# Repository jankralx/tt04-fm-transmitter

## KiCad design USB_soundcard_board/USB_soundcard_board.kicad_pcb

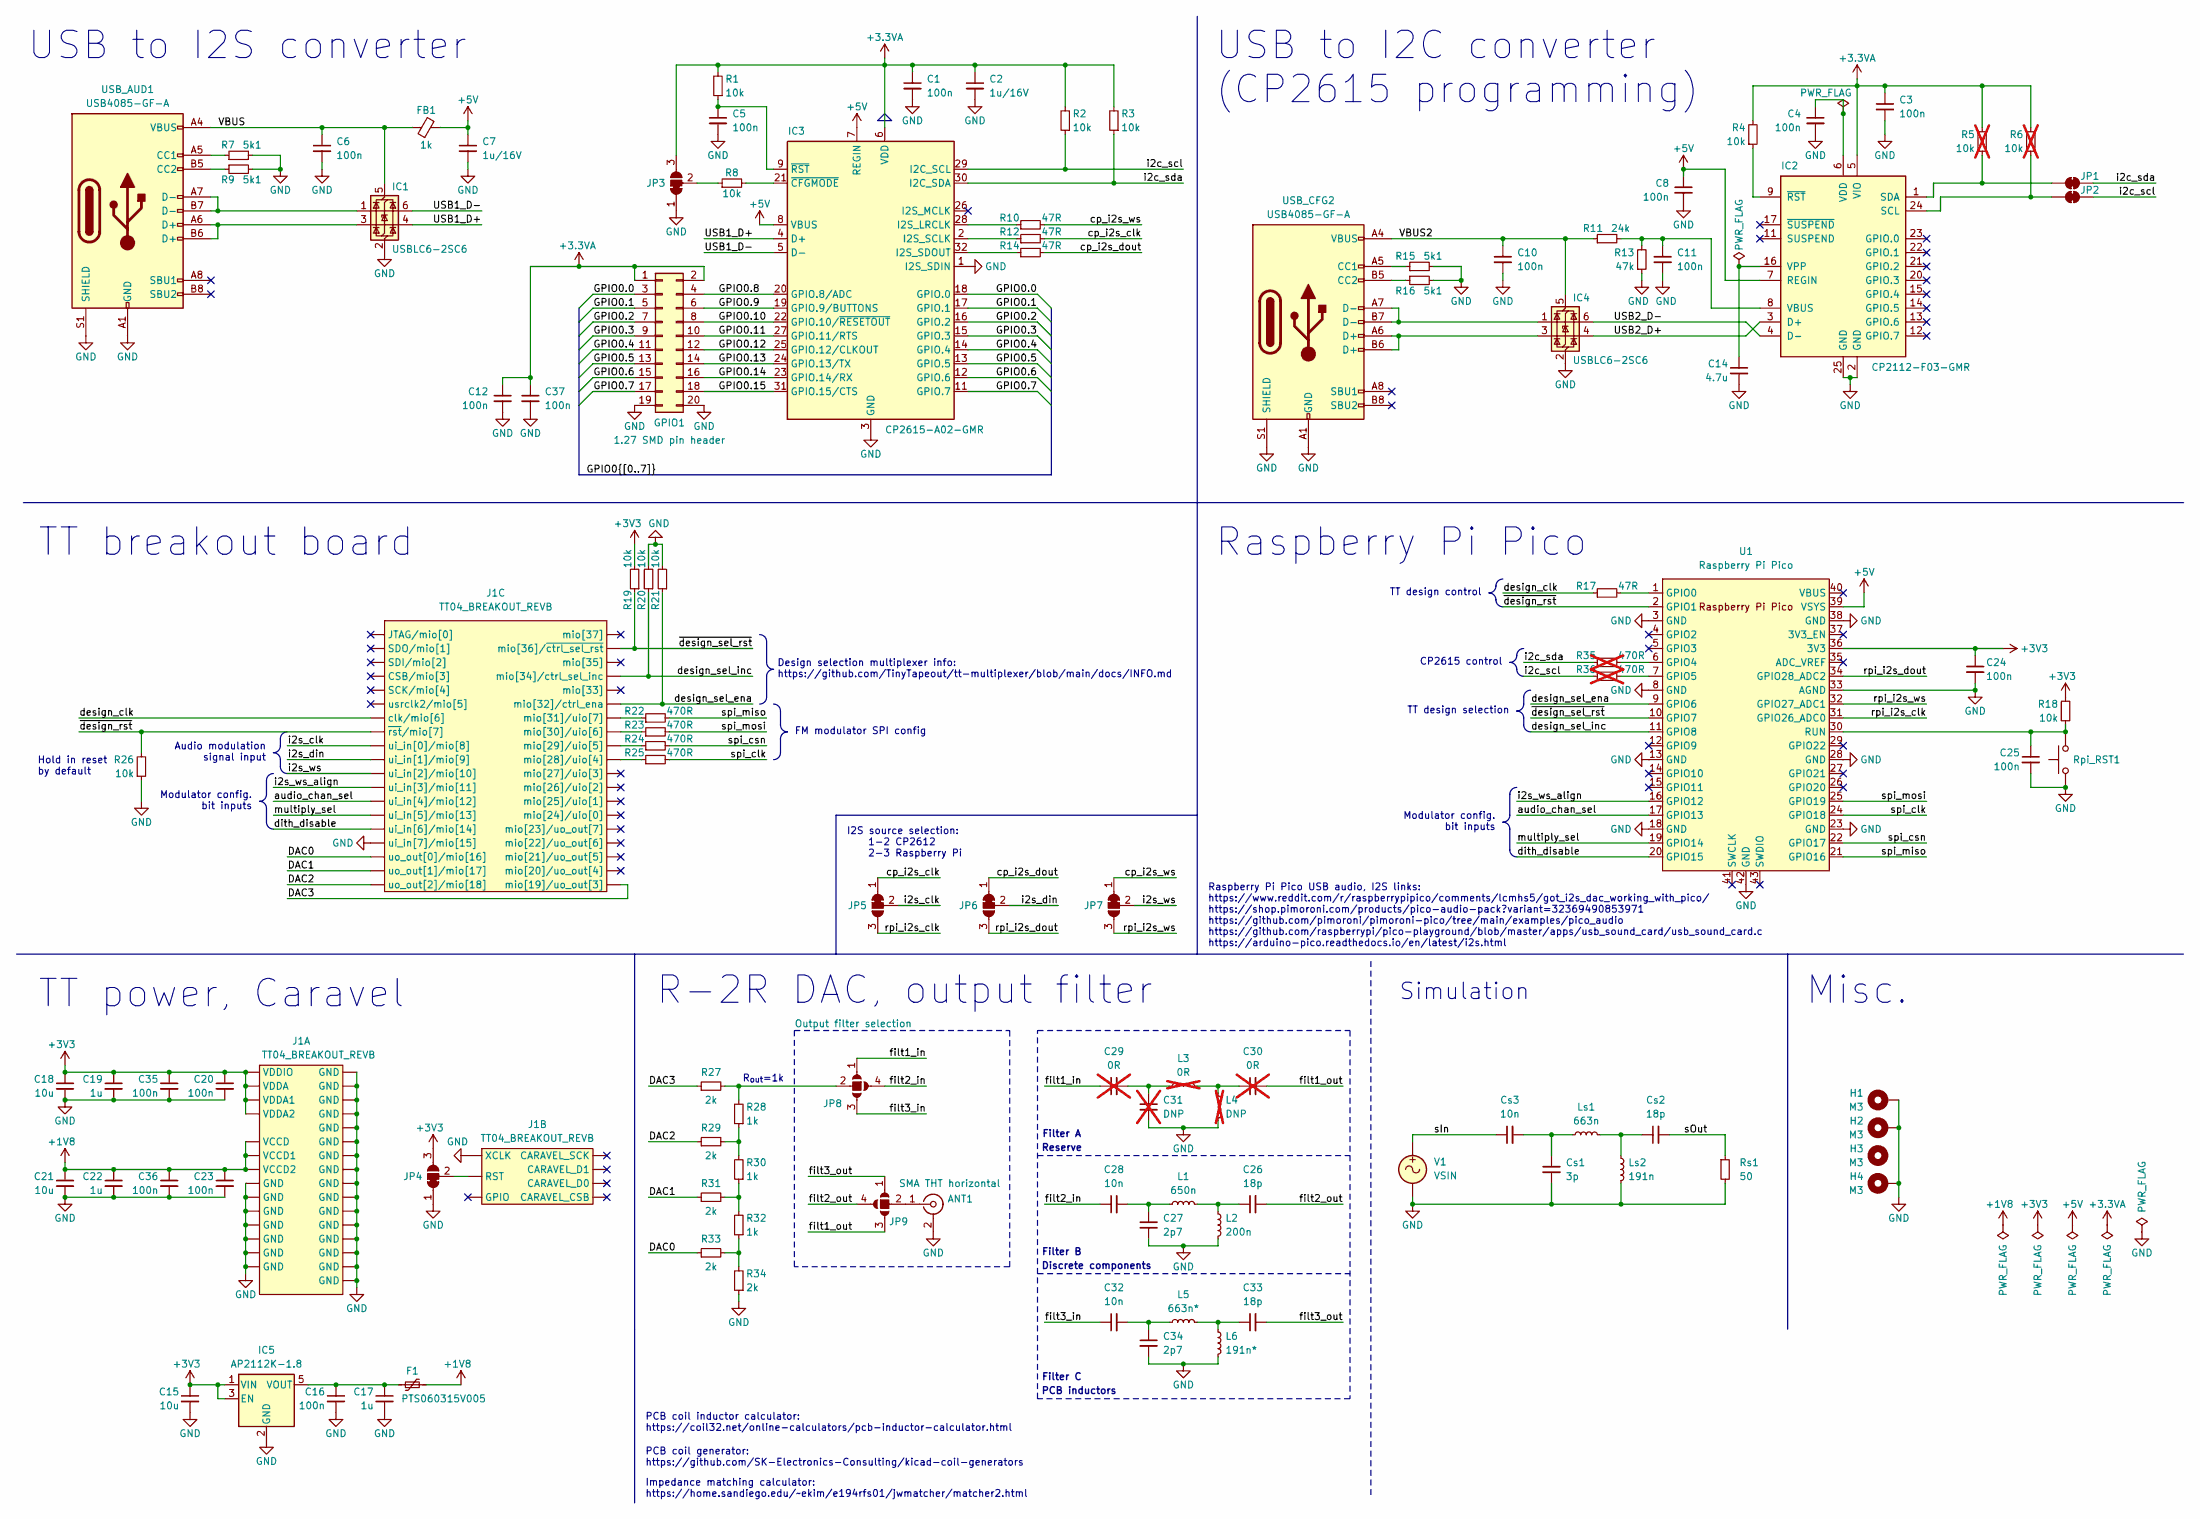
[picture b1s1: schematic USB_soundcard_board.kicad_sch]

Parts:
ANT1: SMA THT horizontal; SMA_Amphenol_132203-12_Horizontal
C1, C3, C4, C5, C6, C8, C10, C11, C12, C16, C20, C23, C24, C25, C35, C36, C37: 100n; C_0603_1608Metric_Pad1.08x0.95mm_HandSolder
C2, C7: 1u/16V; C_0603_1608Metric_Pad1.08x0.95mm_HandSolder
C14: 4.7u; C_0805_2012Metric_Pad1.18x1.45mm_HandSolder
C15, C18, C21: 10u; C_0805_2012Metric_Pad1.18x1.45mm_HandSolder
C17, C19, C22: 1u; C_0603_1608Metric_Pad1.08x0.95mm_HandSolder
C26, C33: 18p; C_0603_1608Metric_Pad1.08x0.95mm_HandSolder
C27, C34: 2p7; C_0603_1608Metric_Pad1.08x0.95mm_HandSolder
C28, C32: 10n; C_0603_1608Metric_Pad1.08x0.95mm_HandSolder
C29, C30: 0R; C_0603_1608Metric_Pad1.08x0.95mm_HandSolder; not fitted
C31: DNP; C_0603_1608Metric_Pad1.08x0.95mm_HandSolder; not fitted
Cs1: 3p
Cs2: 18p
Cs3: 10n
F1: PTS060315V005; Fuse_0603_1608Metric_Pad1.05x0.95mm_HandSolder
FB1: 1k; L_0805_2012Metric_Pad1.15x1.40mm_HandSolder
GPIO1: 1.27 SMD pin header; PinHeader_2x10_P1.27mm_Vertical_SMD
H1, H2, H4: M3; MountingHole_3.2mm_M3_Pad_Via
H3: M3; MountingHole_3.2mm_M3
IC1, IC4: USBLC6-2SC6; SOT-23-6_Handsoldering
IC2: CP2112-F03-GMR; QFN-24-1EP_4x4mm_P0.5mm_EP2.6x2.6mm_ThermalVias
IC3: CP2615-A02-GMR; QFN-32-1EP_5x5mm_P0.5mm_EP3.3x3.3mm_ThermalVias
IC5: AP2112K-1.8; SOT-23-5
J1: TT04_BREAKOUT_REVB; TT04_BREAKOUT_SMB
JP1, JP2: SolderJumper_2_Bridged; SolderJumper-2_P1.3mm_Bridged_RoundedPad1.0x1.5mm
JP3, JP4, JP5, JP6, JP7: SolderJumper_3_Bridged12; SolderJumper-3_P1.3mm_Bridged12_RoundedPad1.0x1.5mm_NumberL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
JP8, JP9: Output filter selection; SolderJumper-4_P1.3mm_Open_RoundedPad1.0x1.5mm_NumberLabels
L1: 650n; L_0603_1608Metric_Pad1.05x0.95mm_HandSolder
L2: 200n; L_0603_1608Metric_Pad1.05x0.95mm_HandSolder
L3: 0R; L_0603_1608Metric_Pad1.05x0.95mm_HandSolder; not fitted
L4: DNP; L_0603_1608Metric_Pad1.05x0.95mm_HandSolder; not fitted
L5: 663n*; Inductor_663nH
L6: 191n*; Inductor_191nH
Ls1: 663n
Ls2: 191n
R1, R2, R3, R4, R8, R18, R19, R20, R21, R26: 10k; R_0603_1608Metric_Pad0.98x0.95mm_HandSolder
R5, R6: 10k; R_0603_1608Metric_Pad0.98x0.95mm_HandSolder; not fitted
R7, R9, R15, R16: 5k1; R_0603_1608Metric_Pad0.98x0.95mm_HandSolder
R10, R12, R14, R17: 47R; R_0603_1608Metric_Pad0.98x0.95mm_HandSolder
R11: 24k; R_0603_1608Metric_Pad0.98x0.95mm_HandSolder
R13: 47k; R_0603_1608Metric_Pad0.98x0.95mm_HandSolder
R22, R23, R24, R25: 470R; R_0603_1608Metric_Pad0.98x0.95mm_HandSolder
R27, R29, R31, R33, R34: 2k; R_0603_1608Metric_Pad0.98x0.95mm_HandSolder
R28, R30, R32: 1k; R_0603_1608Metric_Pad0.98x0.95mm_HandSolder
R35, R36: 470R; R_0603_1608Metric_Pad0.98x0.95mm_HandSolder; not fitted
Rpi_RST1: Raspberry Pi reset; SW_Tactile_SPST_NO_Straight_CK_PTS636Sx25SMTRLFS
Rs1: 50
U1: Raspberry Pi Pico; RPi_Pico_SMD_TH
USB_AUD1: USB4085-GF-A; USB_C_Receptacle_GCT_USB4085
USB_CFG2: USB4085-GF-A; USB_C_Receptacle_GCT_USB4085
V1: VSIN

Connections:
+1V8: C21.1, C22.1, C23.1, C36.1, F1.2, J1.A7 (VCCD), J1.B14 (VCCD2), J1.B16 (VCCD2), J1.B33 (VCCD1), J1.B35 (VCCD1)
+3.3VA: C1.1, C2.1, C3.1, C12.1, C37.1, GPIO1.1, GPIO1.2, IC2.5 (VIO), IC3.6 (VDD), JP3.3 (B), R1.2, R2.2, R3.2, R4.2, R5.2, R6.2
+3V3: C15.1, C18.1, C19.1, C20.1, C24.1, C35.1, IC5.1 (VIN), IC5.3 (EN), J1.A19 (VDDA), J1.B1 (VDDA2), J1.B3 (VDDA2), J1.B15 (VDDIO), J1.B17 (VDDIO), J1.B37 (VDDA1), J1.B39 (VDDA1), JP4.3 (B), R18.2, R19.2, U1.36 (3V3)
+5V: C7.1, C8.1, FB1.2, IC2.7 (REGIN), IC3.7 (REGIN), IC3.8 (VBUS), U1.39 (VSYS)
/DAC0: J1.B32 (uo_out[0]/mio[16]), R33.1
/DAC1: J1.B29 (uo_out[1]/mio[17]), R31.1
/DAC2: J1.B30 (uo_out[2]/mio[18]), R29.1
/DAC3: J1.B27 (mio[19]/uo_out[3]), R27.1
/GPIO0.0: GPIO1.3, IC3.18 (GPIO.0)
/GPIO0.1: GPIO1.5, IC3.17 (GPIO.1)
/GPIO0.2: GPIO1.7, IC3.16 (GPIO.2)
/GPIO0.3: GPIO1.9, IC3.15 (GPIO.3)
/GPIO0.4: GPIO1.11, IC3.14 (GPIO.4)
/GPIO0.5: GPIO1.13, IC3.13 (GPIO.5)
/GPIO0.6: GPIO1.15, IC3.12 (GPIO.6)
/GPIO0.7: GPIO1.17, IC3.11 (GPIO.7)
/GPIO0.8: GPIO1.4, IC3.20 (GPIO.8/ADC)
/GPIO0.9: GPIO1.6, IC3.19 (GPIO.9/BUTTONS)
/GPIO0.10: GPIO1.8, IC3.22 (GPIO.10/~RESETOUT)
/GPIO0.11: GPIO1.10, IC3.27 (GPIO.11/RTS)
/GPIO0.12: GPIO1.12, IC3.25 (GPIO.12/CLKOUT)
/GPIO0.13: GPIO1.14, IC3.24 (GPIO.13/TX)
/GPIO0.14: GPIO1.16, IC3.23 (GPIO.14/RX)
/GPIO0.15: GPIO1.18, IC3.31 (GPIO.15/CTS)
/USB1_D+: IC1.4 (I/O2), IC3.4 (D+)
/USB1_D-: IC1.6 (I/O1), IC3.5 (D-)
/USB2_D+: IC2.3 (D+), IC4.4 (I/O2)
/USB2_D-: IC2.4 (D-), IC4.6 (I/O1)
/VBUS: C6.1, FB1.1, IC1.5 (VBUS), USB_AUD1.A4 (VBUS), USB_AUD1.A9 (VBUS), USB_AUD1.B4 (VBUS), USB_AUD1.B9 (VBUS)
/VBUS2: C10.1, IC4.5 (VBUS), R11.1, USB_CFG2.A4 (VBUS), USB_CFG2.A9 (VBUS), USB_CFG2.B4 (VBUS), USB_CFG2.B9 (VBUS)
/audio_chan_sel: J1.A36 (ui_in[4]/mio[12]), U1.17 (GPIO13)
/cp_i2s_clk: JP5.1 (A), R12.2
/cp_i2s_dout: JP6.1 (A), R14.2
/cp_i2s_ws: JP7.1 (A), R10.2
/design_clk: J1.A28 (clk/mio[6]), R17.1
/design_sel_ena: J1.A1 (mio[32]/ctrl_ena), R21.1, U1.9 (GPIO6)
/design_sel_inc: J1.A3 (mio[34]/ctrl_sel_inc), R20.1, U1.11 (GPIO8)
/dith_disable: J1.A38 (ui_in[6]/mio[14]), U1.20 (GPIO15)
/filt1_in: C29.1, JP8.1 (A)
/filt1_out: C30.2, JP9.3 (B)
/filt2_in: C28.1, JP8.4 (D)
/filt2_out: C26.2, JP9.4 (D)
/filt3_in: C32.1, JP8.3 (B)
/filt3_out: C33.2, JP9.1 (A)
/i2c_scl: IC3.29 (I2C_SCL), JP2.2 (B), R2.1, R36.1
/i2c_sda: IC3.30 (I2C_SDA), JP1.2 (B), R3.1, R35.1
/i2s_clk: J1.A32 (ui_in[0]/mio[8]), JP5.2 (C)
/i2s_din: J1.A33 (ui_in[1]/mio[9]), JP6.2 (C)
/i2s_ws: J1.A34 (ui_in[2]/mio[10]), JP7.2 (C)
/i2s_ws_align: J1.A35 (ui_in[3]/mio[11]), U1.16 (GPIO12)
/multiply_sel: J1.A37 (ui_in[5]/mio[13]), U1.19 (GPIO14)
/rpi_i2s_clk: JP5.3 (B), U1.31 (GPIO26_ADC0)
/rpi_i2s_dout: JP6.3 (B), U1.34 (GPIO28_ADC2)
/rpi_i2s_ws: JP7.3 (B), U1.32 (GPIO27_ADC1)
/spi_clk: R25.2, U1.24 (GPIO18)
/spi_csn: R24.2, U1.22 (GPIO17)
/spi_miso: R22.2, U1.21 (GPIO16)
/spi_mosi: R23.2, U1.25 (GPIO19)
/~design_rst: J1.A31 (~rst/mio[7]), R26.2, U1.2 (GPIO1)
/~design_sel_rst: J1.A8 (mio[36]/~ctrl_sel_rst), R19.1, U1.10 (GPIO7)
GND: ANT1.2 (Ext), C1.2, C2.2, C3.2, C4.2, C5.2, C6.2, C7.2, C8.2, C10.2, C11.2, C12.2, C14.2, C15.2, C16.2, C17.2, C18.2, C19.2, C20.2, C21.2, C22.2, C23.2, C24.2, C25.2, C27.2, C31.2, C34.2, C35.2, C36.2, C37.2, Cs1.2, GPIO1.19, GPIO1.20, H1.1, H2.1, H4.1, IC1.2 (GND), IC2.2 (GND), IC2.25 (GND), IC3.1 (I2S_SDIN), IC3.3 (GND), IC3.33 (GND), IC4.2 (GND), IC5.2 (GND), J1.A2 (GND), J1.A9 (GND), J1.A10 (GND), J1.A11 (XCLK), J1.A15 (GND), J1.A20 (GND), J1.A25 (GND), J1.A29 (GND), J1.A30 (GND), J1.A39 (ui_in[7]/mio[15]), J1.A40 (GND), J1.B2 (GND), J1.B4 (GND), J1.B12 (GND), J1.B13 (GND), J1.B18 (GND), J1.B19 (GND), J1.B20 (GND), J1.B24 (GND), J1.B25 (GND), J1.B31 (GND), J1.B34 (GND), J1.B36 (GND), J1.B38 (GND), J1.B40 (GND), JP3.1 (A), JP4.1 (A), L2.2, L4.2, L6.2, Ls2.2, R7.2, R9.2, R13.1, R15.2, R16.2, R20.2, R21.2, R26.1, R34.1, Rpi_RST1.1, Rs1.2, U1.3 (GND), U1.8 (GND), U1.13 (GND), U1.18 (GND), U1.23 (GND), U1.28 (GND), U1.33 (AGND), U1.38 (GND), U1.42 (GND), USB_AUD1.A1 (GND), USB_AUD1.A12 (GND), USB_AUD1.B1 (GND), USB_AUD1.B12 (GND), USB_AUD1.S1 (SHIELD), USB_CFG2.A1 (GND), USB_CFG2.A12 (GND), USB_CFG2.B1 (GND), USB_CFG2.B12 (GND), USB_CFG2.S1 (SHIELD), V1.2
unnamed: ANT1.1 (In), JP9.2 (C)
unnamed: C26.1, L1.2, L2.1
unnamed: C27.1, C28.2, L1.1
unnamed: C29.2, C31.1, L3.1
unnamed: C30.1, L3.2, L4.1
unnamed: C32.2, C34.1, L5.1
unnamed: C33.1, L5.2, L6.1
unnamed: Cs1.1, Cs3.2, Ls1.1
unnamed: Cs2.1, Ls1.2, Ls2.1
unnamed: Cs2.2, Rs1.1
unnamed: Cs3.1, V1.1
unnamed: IC1.1 (I/O1), USB_AUD1.A7 (D-), USB_AUD1.B7 (D-)
unnamed: IC1.3 (I/O2), USB_AUD1.A6 (D+), USB_AUD1.B6 (D+)
unnamed: IC2.24 (SCL), JP2.1 (A), R6.1
unnamed: IC2.1 (SDA), JP1.1 (A), R5.1
unnamed: C11.1, IC2.8 (VBUS), R11.2, R13.2
unnamed: C4.1, IC2.6 (VDD)
unnamed: C14.1, IC2.16 (VPP)
unnamed: IC2.9 (~RST), R4.1
unnamed: IC3.28 (I2S_LRCLK), R10.1
unnamed: IC3.2 (I2S_SCLK), R12.1
unnamed: IC3.32 (I2S_SDOUT), R14.1
unnamed: IC3.21 (~CFGMODE), R8.2
unnamed: C5.1, IC3.9 (~RST), R1.1
unnamed: IC4.1 (I/O1), USB_CFG2.A7 (D-), USB_CFG2.B7 (D-)
unnamed: IC4.3 (I/O2), USB_CFG2.A6 (D+), USB_CFG2.B6 (D+)
unnamed: C16.1, C17.1, F1.1, IC5.5 (VOUT)
unnamed: J1.A12 (RST), JP4.2 (C)
unnamed: J1.B7 (mio[28]/uio[4]), R25.1
unnamed: J1.B8 (mio[29]/uio[5]), R24.1
unnamed: J1.B5 (mio[30]/uio[6]), R23.1
unnamed: J1.B6 (mio[31]/uio[7]), R22.1
unnamed: JP3.2 (C), R8.1
unnamed: JP8.2 (C), R27.2, R28.2
unnamed: R28.1, R29.2, R30.2
unnamed: R30.1, R31.2, R32.2
unnamed: R32.1, R33.2, R34.2
unnamed: R17.2, U1.1 (GPIO0)
unnamed: R35.2, U1.6 (GPIO4)
unnamed: R36.2, U1.7 (GPIO5)
unnamed: C25.1, R18.1, Rpi_RST1.2, U1.30 (RUN)
unnamed: R7.1, USB_AUD1.A5 (CC1)
unnamed: R9.1, USB_AUD1.B5 (CC2)
unnamed: R15.1, USB_CFG2.A5 (CC1)
unnamed: R16.1, USB_CFG2.B5 (CC2)

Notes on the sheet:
Modulator config. bit inputs
TT power, Caravel
I2S source selection: 1-2 CP2612 2-3 Raspberry Pi
Design selection multiplexer info: https://github.com/TinyTapeout/tt-multiplexer/blob/main/docs/INFO.md
USB to I2S converter
CP2615 control
Filter A
PCB inductors
PCB coil generator: https://github.com/SK-Electronics-Consulting/kicad-coil-generators
Audio modulation signal input
Raspberry Pi Pico USB audio, I2S links: https://www.reddit.com/r/raspberrypipico/comments/lcmhs5/got_i2s_dac_working_with_pico/ https://shop.pimoroni.com/products/pico-audio-pack?variant=32369490853971 https://github.com/pimoroni/pimoroni-pico/tree/main/examples/pico_audio https://github.com/raspbe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
Misc.
PCB coil inductor calculator: https://coil32.net/online-calculators/pcb-inductor-calculator.html
Impedance matching calculator: https://home.sandiego.edu/~ekim/e194rfs01/jwmatcher/matcher2.html
Discrete components
Hold in reset by default
Filter B
Filter C
R-2R DAC, output filter
USB to I2C converter (CP2615 programming)
R_{out}=1k
TT design control
TT breakout board
FM modulator SPI config
TT design selection
Reserve
Simulation
Raspberry Pi Pico

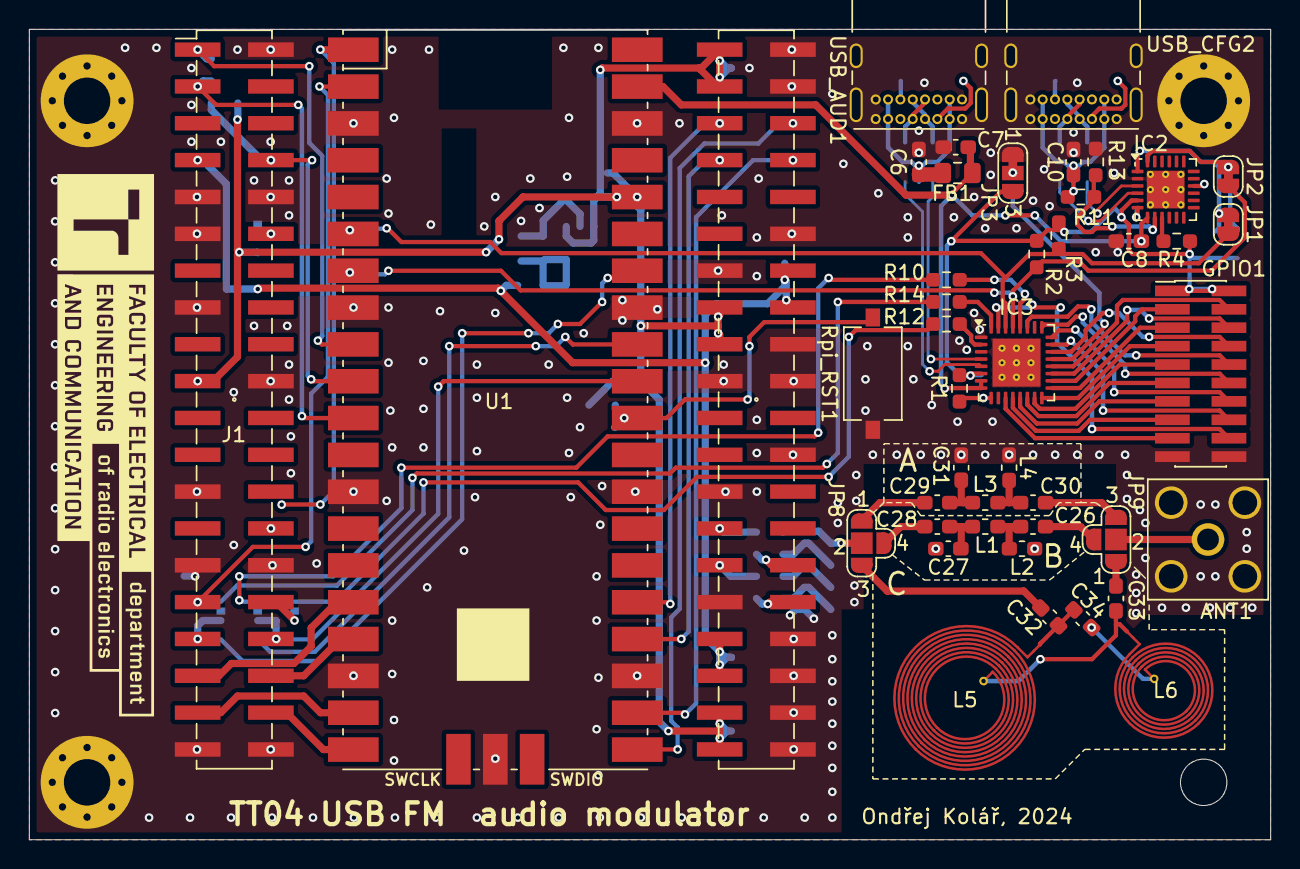
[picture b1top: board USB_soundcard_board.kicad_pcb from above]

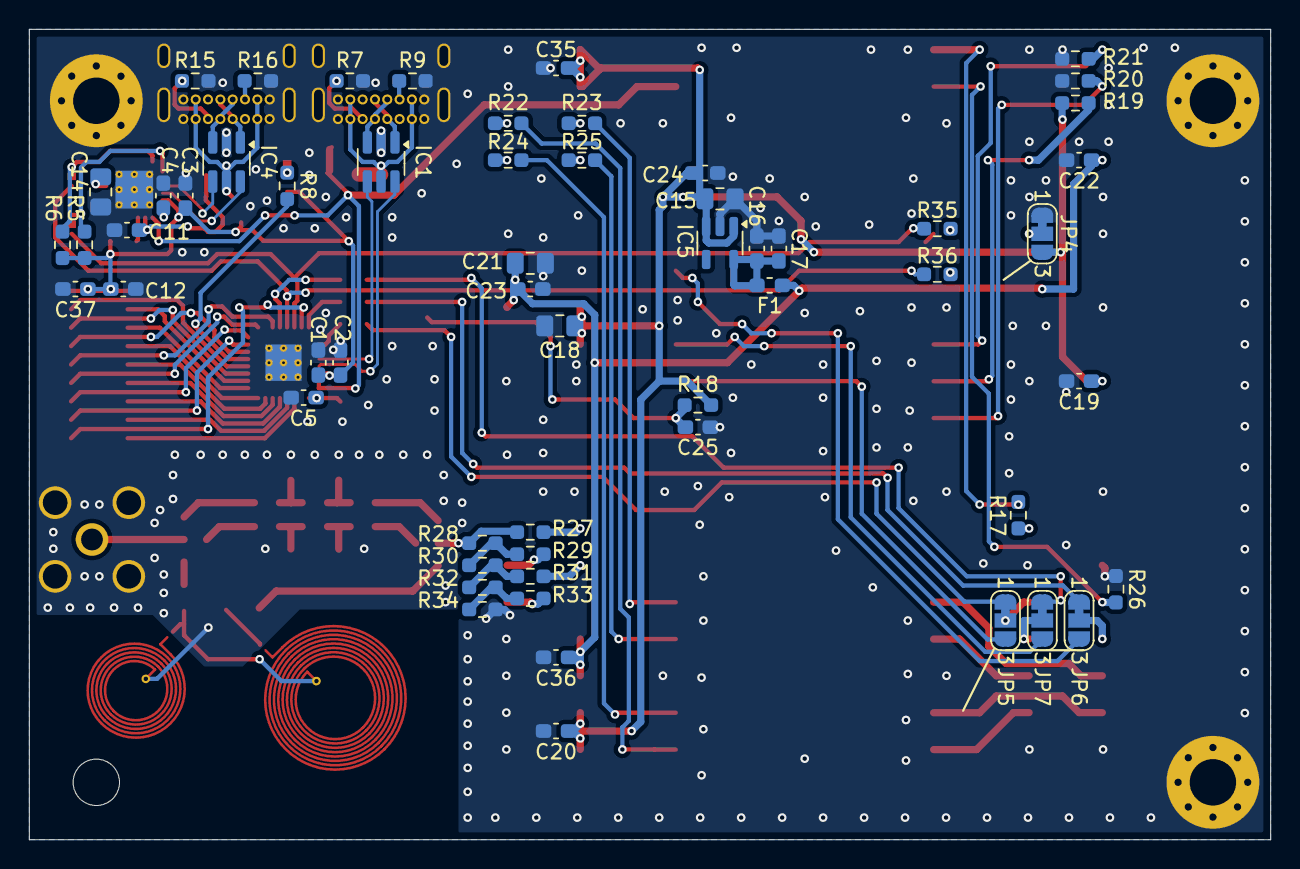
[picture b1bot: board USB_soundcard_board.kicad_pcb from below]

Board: 2 copper layers, 85.6 x 55.9 mm, 104 parts (57 on the bottom side), 102 nets.

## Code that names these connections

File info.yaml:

--- 
# TinyTapeout project information
project:
  wokwi_id:    0        # If using wokwi, set this to your project's ID

# If using an HDL, set wokwi_id as 0 and uncomment and list your source files here. 
# Source files must be in ./src and you must list each source file separately
  source_files:        
    - fm_modulator.v
    - i2s_rx.v
    - tt_um_fm_transmitter.v
    - cdc_slow2fast_bus.v
    - spi_config.v
  top_module:  "tt_um_fm_transmitter"      # Put the name of your top module here, must start with "tt_um_". Make it unique by including your github username

# How many tiles your design occupies? A single tile is about 167x108 uM.
  tiles: "1x1"    # Valid values: 1x1, 1x2, 2x2, 4x2 or 8x2

# Keep a track of the submission yaml
yaml_version: 4

# As everyone will have access to all designs, try to make it easy for someone new to your design to know what
# it does and how to operate it. This info will be automatically collected and used to make a datasheet for the chip.
#
# Here is a great example: https://github.com/davidsiaw/tt02-davidsiaw-stackcalc/blob/38c5647f83aad2aec675d566aa3d67b98f0aac81/info.yaml
documentation: 
  author:       "Jan Kral (<jan.kral@vut.cz>), Ondrej Kolar (<ondrej.kolar@vut.cz>)"               # Your name
  title:        "FM Transmitter"                       # Project title
  language:     "Verilog"                              # other examples include Verilog, Amaranth, VHDL, etc
  description:  "FM transmitter with I2S input"        # Short description of what your project does

# Longer description of how the project works. You can use standard markdown format.
  how_it_works: |
    Our design takes an audio signal and modulates it to a higher carrier frequency, using [*FM modulation*](https://en.wikipedia.org/wiki/Frequency_modulation). The modulator in our design is based on a [*numerically controlled oscillator*](https://en.wikipedia.org/wiki/Numerically_controlled_oscillator) (NCO) with several modifications.
    
    The *frequency control word*, which increments the *phase accumulator*, is being added with the audio signal. This results in the phase increments proportional to the current audio sample level. The variation directly determines the actual shift of the output signal frequency. For the conversion of phase to a harmonic signal (sine wave) NCOs usually use look-up tables or [*CORDIC algorithm*](https://en.wikipedia.org/wiki/CORDIC). However, both of these methods are resource-heavy, therefore the design adopts a very rough, piecewise linearized approximation of the sine function. The main upside of this approach is the lightweight implementation, which utilizes only simple bit-shifting and addition operations.
    
    ![Our harmonic function approximation](doc/figureApproximation.png)
    
    Since the output digital-to-analog converter suggested below is not followed by a [*reconstruction filter*](https://en.wikipedia.org/wiki/Reconstruction_filter), the output signal will not be present only on a single frequency but also on several higher ones, sometimes called *mirrors* (as they appear on frequencies mirrored by the sampling frequency and its multiples). Thanks to this, it is possible to get the signal in the range of FM broadcast band, even with the sampling frequency lower than the carrier frequency.
    

# Instructions on how someone could test your project, include things like what buttons do what and how to set the clock if needed
  how_to_test:  |
    **Disclaimer! Our design is not intended for real *on air* use. Any signals generated by our design are far from ideal and require proper filtering. Improper use will most probably violate your local regulations. Use only at your own risk!**
    
    ![Schematic of a simple DAC](doc/schematicDAC.png)

    For testing the design you need to provide an audio source using the I2S bus interface. You can use for example Raspberry Pi. For the output, you need to build a DAC. A simple [*R–2R resistor ladder network*](https://en.wikipedia.org/wiki/Resistor_ladder#R%E2%80%932R_resistor_ladder_network_(digital_to_analog_conversion)) should be enough for testing. The schematic is provided above.
   

# A description of what the inputs do (e.g. red button, SPI CLK, SPI MOSI, etc).
  inputs:               
    - i2s_clk
    - i2s_din
    - i2s_ws
    - i2s_ws_align_pin
    - audio_chan_sel_pin
    - multiply_sel_pin
    - dith_disable_pin
    - none
# A description of what the outputs do (e.g. status LED, SPI MISO, etc)
  outputs:
    - dac[0] (LSB)
    - dac[1]
    - dac[2]
    - dac[3] (MSB)
    - none
    - none
    - none
    - none
# A description of what the bidirectional I/O pins do (e.g. I2C SDA, I2C SCL, etc)
  bidirectional:
    - none
    - none
    - none
    - none
    - spi_clk (in)
    - spi_csn (in)
    - spi_mosi (in)
    - spi_miso (inout)

# The following fields are optional
  tag:          "fm, modulator, audio, music, i2s"              # comma separated list of tags: test, encryption, experiment, clock, animation, utility, industrial, pwm, fpga, alu, microprocessor, risc, riscv, sensor, signal generator, fft, filter, music, bcd, sound, serial, timer, random number generator, calculator, decoder, counter, puzzle, multiplier, game, oscillator,
  external_hw:  "4-bit R-2R DAC, I2S source, SPI (optional)"    # Describe any external hardware needed
  discord:      "xkolar74_10263"       # Your discord handle, used for communication and automatically assigning tapeout role after a submission
  doc_link:     "https://github.com/jankralx/tt04-fm-transmitter/blob/main/README.md"      # URL to longer form documentation, eg the README.md in your repository
  clock_hz:     50000000               # Clock frequency in Hz (if required)
  picture:      "doc/diagram.png"      # relative path to a picture in your repository (must be 512kb or less)

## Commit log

2023-08-30 initial commit of files tested on FPGA for FM transmitter
2023-09-04 (src) fixing real type and renaming top design to comply with rules of TT
2023-09-04 (yaml) changing to 1x1 and fixing description
2023-09-04 (documentation) Updated info.yaml and added diagram of the design to 'doc' folder
2023-09-04 (documentation) Added design diagram in PNG, fixed frequency in info.yaml
2023-09-07 (src) spi configuration, FM modulator parameters set by signals
2023-09-07 (info yaml) updated info.yaml to reflect newly defined pins, added source files, and extarnal hardware
2023-09-07 (info yaml) removing URL from names
2023-09-07 (info yaml, src) fixing emails in info yaml and uio_oe in top module
2023-09-07 (src) fixing same instance name in top module
2023-09-07 (src) fixing parameters of modulator instance and negedge sensitivity of spi_clk signal
2023-09-07 (src) chaning MOSI to be given at output on posedge of spi_clk
2023-09-07 (src) fixing two drivers for single nets in top module
2023-09-07 (src) commenting out spi_config to isolate the error source
2023-09-07 (src) adding part of spi_config to isolate the error source
2023-09-07 (src) fixing missing bits in dith_fact assignemnt
2023-09-07 Added some documentation
2023-09-07 Added more documentation and schematics.
2023-09-07 Fixed schematic sizes.
2023-09-07 (FGPA-USB-Device) adding as submodule
2023-09-07 (src) removed unused debug code in spi_config.v
2023-09-07 (src) adding USB support, needs to be connected to FM modulator
2023-09-07 (src) fixing duplicate port assignment in top module
2023-09-08 (src) fixing output to gnd connection in top module
2023-09-08 (src) changing df_inc to df_inc_coef and df_inc_fact for smaller footprint
2023-09-08 (src) fixing selection of multiplexer by df_inc_fact
2023-09-08 (src) trying another implementation of the multiplexer because compilation fails
2023-09-08 (src) fixing width of df_inc_fact and df_inc_coef
2023-09-08 (src) adding negedge sensitive register for spi_miso, and ILAs generated only when part of FPGA project
2023-09-08 (src) version tested on FPGA, fixing some mess with signed wires in FM modulator
2023-09-08 (src) removing negedge register to isolate error source
2023-09-08 (src) fixing asynchronous reset of spi_miso output register
2023-09-08 (src) description modified
2023-09-08 (doc) removing USB from doc
2023-09-08 (doc) fixing margins of schematic-DAC.pdf
2023-09-08 removed submodule of USB as this is not needed
2023-09-08 (doc) adding missing DAC schematic
2023-09-18 (doc) Converted images to PNG.
2023-09-18 (doc) Fixed resolution of images.
2024-08-28 (python) setting python file for FM transmitter
2024-09-09 Added KiCad project of USB soundcard baseboard for the TT04 breakout board.
2024-09-18 Added MicroPython code for the Raspberry Pi Pico on the USB board.
2024-09-18 Post-prototype tweaks in USB board schematic
2025-01-20 Added filter input impedance trace to the simulation.
2025-01-20 (USB_soundcard_board) Added results of filter measurements.
2025-02-19 (doc) Added SDR screenshots.
2025-02-19 (doc) Added photos of the FM modulator board.
2025-04-11 Updated the USB board Python code
2025-04-11 Added some measurement data
2025-04-11 Added oscillogram of modulated signal
